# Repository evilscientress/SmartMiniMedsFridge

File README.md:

# Smart Mini Meds Fridge

A PCB to make a cheap mini fridge smart and more suitable for storing medication.

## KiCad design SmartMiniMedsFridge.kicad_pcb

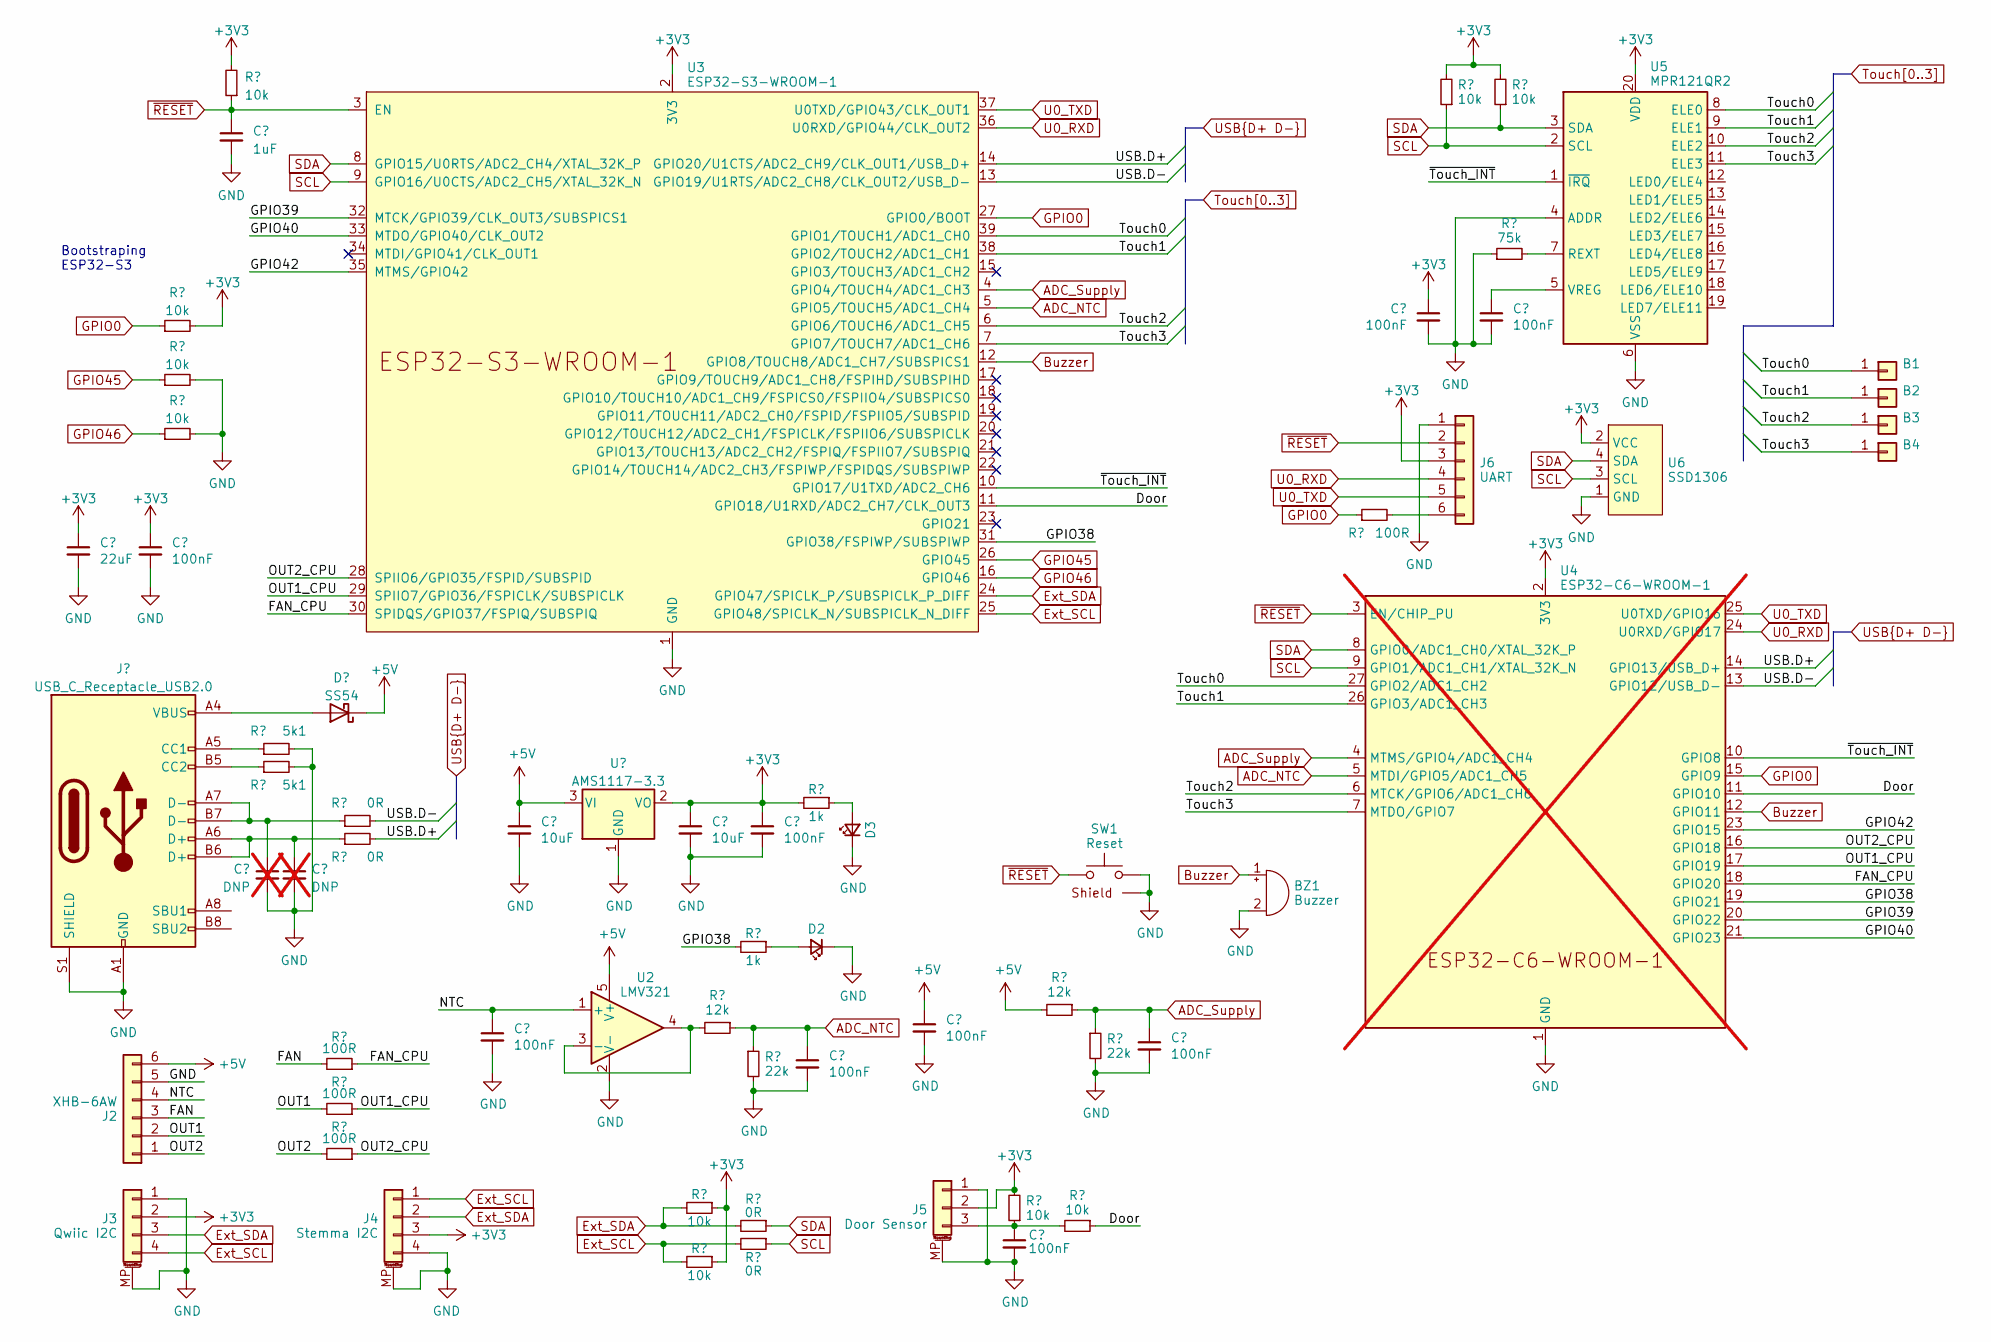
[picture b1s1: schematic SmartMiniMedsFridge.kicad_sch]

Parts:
B1, B2, B3, B4: Spring Contact; PinHeader_1x01_P2.54mm_Vertical; LCSC C5143801
BZ1: Buzzer; Buzzer_TDK_PS1240P02BT_D12.2mm_H6.5mm; LCSC C76871
C1: 22uF; C_0603_1608Metric; LCSC C59461
C2, C6, C9, C10, C11, C12, C13, C14, C15: 100nF; C_0603_1608Metric; LCSC C14663
C3: 1uF; C_0603_1608Metric; LCSC C15849
C4, C5: DNP; C_0603_1608Metric; not fitted
C7, C8: 10uF; C_0603_1608Metric; LCSC C96446
D1: SS54; D_SMA; LCSC C22452
D2: White; LED_0603_1608Metric; LCSC C2290
D3: Red; LED_0603_1608Metric; LCSC C2286
J1: USB_C_Receptacle_USB2.0; USB_C_Receptacle_G-Switch_GT-USB-7051x; LCSC C2843970
J2: XHB-6AW; JST_XH_S6B-XH-A-1_1x06_P2.50mm_Horizontal; LCSC C2905003
J3: Qwiic I2C; JST_SH_SM04B-SRSS-TB_1x04-1MP_P1.00mm_Horizontal; LCSC C160404
J4: Stemma I2C; JST_PH_S4B-PH-SM4-TB_1x04-1MP_P2.00mm_Horizontal; LCSC C265332
J5: Door Sensor; JST_PH_S3B-PH-SM4-TB_1x03-1MP_P2.00mm_Horizontal; LCSC C265101
J6: UART; PinHeader_1x06_P2.54mm_Vertical
R1, R2, R3, R4, R12, R13, R20, R22, R25, R26: 10k; R_0603_1608Metric; LCSC C25804
R5, R6: 5k1; R_0603_1608Metric; LCSC C23186
R7, R8, R9, R24: 100R; R_0603_1608Metric; LCSC C22775
R10, R11, R14, R15: 0R; R_0603_1608Metric; LCSC C21189
R16, R21: 12k; R_0603_1608Metric; LCSC C22790
R17, R23: 22k; R_0603_1608Metric; LCSC C31850
R18, R19: 1k; R_0603_1608Metric; LCSC C21190
R27: 75k; R_0603_1608Metric; LCSC C23242
SW1: Reset; SW_Push_1P1T-SH_NO_CK_KMR2xxG; LCSC C221675
U1: AMS1117-3.3; SOT-223-3_TabPin2; LCSC C6186
U2: LMV321; SOT-23-5; LCSC C7972
U3: ESP32-S3-WROOM-1
U4: ESP32-C6-WROOM-1; not fitted
U5: MPR121QR2; UQFN-20_3x3mm_P0.4mm; LCSC C91322
U6: SSD1306; SSD1306_I2C_0.96in

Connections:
+3V3: C1.1, C2.1, C8.1, C9.1, C14.1, J3.2, J4.3, J5.2, J6.3, R1.2, R4.2, R12.1, R13.1, R19.2, R20.2, R25.2, R26.2, U1.2 (VO), U3.2 (3V3), U4.2 (3V3), U5.20 (VDD), U6.2 (VCC)
+5V: C7.1, C11.1, D1.1 (K), J2.6, R21.2, U1.3 (VI), U2.5 (V+)
/Door: R22.1, U3.11 (GPIO18/U1RXD/ADC2_CH7/CLK_OUT3), U4.11 (GPIO10)
/FAN: J2.3, R7.2
/FAN_CPU: R7.1, U3.30 (SPIDQS/GPIO37/FSPIQ/SUBSPIQ), U4.18 (GPIO20)
/GPIO38: R18.2, U3.31 (GPIO38/FSPIWP/SUBSPIWP), U4.19 (GPIO21)
/GPIO39: U3.32 (MTCK/GPIO39/CLK_OUT3/SUBSPICS1), U4.20 (GPIO22)
/GPIO40: U3.33 (MTDO/GPIO40/CLK_OUT2), U4.21 (GPIO23)
/GPIO42: U3.35 (MTMS/GPIO42), U4.23 (GPIO15)
/NTC: C6.1, J2.4, U2.1 (+)
/OUT1: J2.2, R8.2
/OUT1_CPU: R8.1, U3.29 (SPIIO7/GPIO36/FSPICLK/SUBSPICLK), U4.17 (GPIO19)
/OUT2: J2.1, R9.2
/OUT2_CPU: R9.1, U3.28 (SPIIO6/GPIO35/FSPID/SUBSPID), U4.16 (GPIO18)
/~Touch_INT: U3.10 (GPIO17/U1TXD/ADC2_CH6), U4.10 (GPIO8), U5.1 (~IRQ)
ADC_NTC: C10.1, R16.1, R17.1, U3.5 (GPIO5/TOUCH5/ADC1_CH4), U4.5 (MTDI/GPIO5/ADC1_CH5)
ADC_Supply: C13.1, R21.1, R23.1, U3.4 (GPIO4/TOUCH4/ADC1_CH3), U4.4 (MTMS/GPIO4/ADC1_CH4)
Buzzer: BZ1.1 (-), U3.12 (GPIO8/TOUCH8/ADC1_CH7/SUBSPICS1), U4.12 (GPIO11)
Ext_SCL: J3.4, J4.1, R13.2, R15.2, U3.25 (GPIO48/SPICLK_N/SUBSPICLK_N_DIFF)
Ext_SDA: J3.3, J4.2, R12.2, R14.2, U3.24 (GPIO47/SPICLK_P/SUBSPICLK_P_DIFF)
GND: BZ1.2 (+), C1.2, C2.2, C3.2, C4.2, C5.2, C6.2, C7.2, C8.2, C9.2, C10.2, C11.2, C12.2, C13.2, C14.2, C15.2, D2.1 (K), D3.1 (K), J1.A1 (GND), J1.A12 (GND), J1.B1 (GND), J1.B12 (GND), J1.S1 (SHIELD), J2.5, J3.1, J3.MP (MountPin), J4.4, J4.MP (MountPin), J5.1, J5.MP (MountPin), J6.1, R2.2, R3.2, R5.2, R6.2, R17.2, R23.2, R27.1, SW1.2, SW1.SH (Shield), U1.1 (GND), U2.2 (V-), U3.1 (GND), U3.40 (GND), U3.41 (GND), U4.1 (GND), U4.28 (GND), U4.29 (GND), U5.4 (ADDR), U5.6 (VSS), U6.1 (GND)
GPIO0: R1.1, R24.1, U3.27 (GPIO0/BOOT), U4.15 (GPIO9)
GPIO45: R2.1, U3.26 (GPIO45)
GPIO46: R3.1, U3.16 (GPIO46)
unnamed: C4.1, J1.A7 (D-), J1.B7 (D-), R10.1
unnamed: C5.1, J1.A6 (D+), J1.B6 (D+), R11.1
unnamed: D1.2 (A), J1.A4 (VBUS), J1.A9 (VBUS), J1.B4 (VBUS), J1.B9 (VBUS)
unnamed: D2.2 (A), R18.1
unnamed: D3.2 (A), R19.1
unnamed: J1.A5 (CC1), R5.1
unnamed: J1.B5 (CC2), R6.1
unnamed: C12.1, J5.3, R20.1, R22.2
unnamed: J6.6, R24.2
unnamed: R16.2, U2.3 (-), U2.4
unnamed: R27.2, U5.7 (REXT)
unnamed: C15.1, U5.5 (VREG)
SCL: R15.1, R25.1, U3.9 (GPIO16/U0CTS/ADC2_CH5/XTAL_32K_N), U4.9 (GPIO1/ADC1_CH1/XTAL_32K_N), U5.2 (SCL), U6.3 (SCL)
SDA: R14.1, R26.1, U3.8 (GPIO15/U0RTS/ADC2_CH4/XTAL_32K_P), U4.8 (GPIO0/ADC1_CH0/XTAL_32K_P), U5.3 (SDA), U6.4 (SDA)
Touch0: B1.1, U3.39 (GPIO1/TOUCH1/ADC1_CH0), U4.27 (GPIO2/ADC1_CH2), U5.8 (ELE0)
Touch1: B2.1, U3.38 (GPIO2/TOUCH2/ADC1_CH1), U4.26 (GPIO3/ADC1_CH3), U5.9 (ELE1)
Touch2: B3.1, U3.6 (GPIO6/TOUCH6/ADC1_CH5), U4.6 (MTCK/GPIO6/ADC1_CH6), U5.10 (ELE2)
Touch3: B4.1, U3.7 (GPIO7/TOUCH7/ADC1_CH6), U4.7 (MTDO/GPIO7), U5.11 (ELE3)
U0_RXD: J6.4, U3.36 (U0RXD/GPIO44/CLK_OUT2), U4.24 (U0RXD/GPIO17)
U0_TXD: J6.5, U3.37 (U0TXD/GPIO43/CLK_OUT1), U4.25 (U0TXD/GPIO16)
USB.D+: R11.2, U3.14 (GPIO20/U1CTS/ADC2_CH9/CLK_OUT1/USB_D+), U4.14 (GPIO13/USB_D+)
USB.D-: R10.2, U3.13 (GPIO19/U1RTS/ADC2_CH8/CLK_OUT2/USB_D-), U4.13 (GPIO12/USB_D-)
~RESET: C3.1, J6.2, R4.1, SW1.1, U3.3 (EN), U4.3 (EN/CHIP_PU)

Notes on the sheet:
Bootstraping ESP32-S3

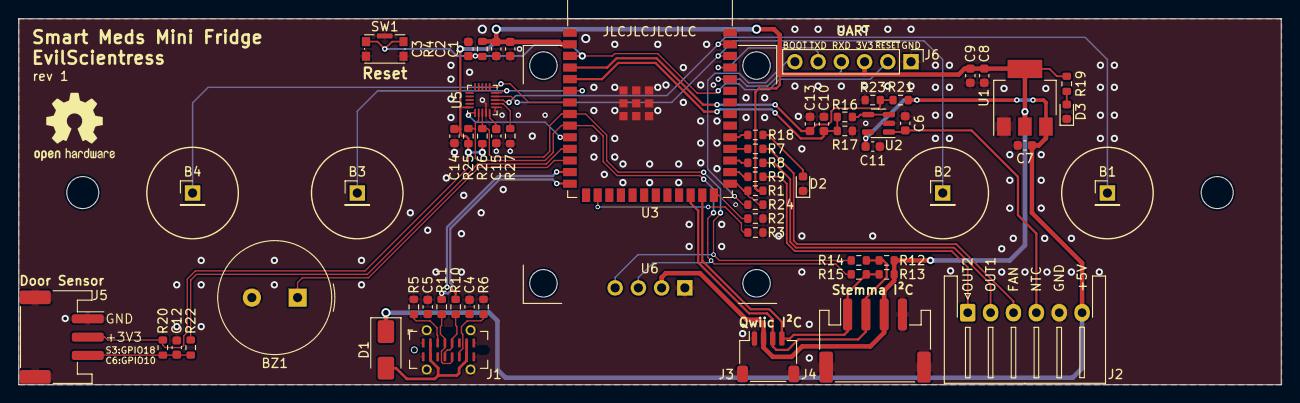
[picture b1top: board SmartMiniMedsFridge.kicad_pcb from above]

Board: 2 copper layers, 138.0 x 40.0 mm, 62 parts (0 on the bottom side), 44 nets.

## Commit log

2023-07-11 initial import
2023-07-11 pre re-arrangement because of collision with case
2024-01-26 1st production version
2024-01-26 Readme and license
